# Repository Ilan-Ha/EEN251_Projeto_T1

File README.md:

# Bebedouro Inteligente para Pets

## Integrantes do Grupo:
- Diego Mourão Oliveira
- Ilan Hameiry
- Luca Lopes Martinho

## Descrição do Projeto

O projeto consiste no desenvolvimento de um dispositivo IoT voltado para o fornecimento de água corrente para animais de estimação (pets), com foco em uso residencial.

O objetivo principal é oferecer uma forma mais atrente e confortável de hidratação para o animal, simulando o fluxo de água corrente, além de monitorar a frequência com que o pet utiliza o bebedouro.

O sistema será ativado automaticamente apenas quando houver presença do animal próxima ao dispositivo, evitando desperdício de energia e água.

## Funcionamento do Sistema

O bebedouro funcionará em ciclo contínuo de circulação de água entre a bomba e o reservatório, simulando água corrente.

Por meio de um sensor de presença por distância (ultrassônico), o sistema será ativado automaticamente quando o animal se aproximar.

Após a detecção, o dispositivo permanecerá ligado por alguns segundos mesmo após a ausência de presença, garantindo tempo suficiente para o pet se hidratar.

Além disso, o sistema contará com:

- Iluminação interna por LEDs, acionada automaticamente quando a luminosidade do ambiente estiver baixa;
- Display informativo com dados importantes de uso;
- Monitoramento do nível de água no reservatório;
- Alertas de nível baixo de água;
- Botão de ativação manual;
- Botão de reset do sistema;
- Envio de notificações e informações para um software externo via Bluetooth.

## Objetivos do Projeto

- Melhorar a experiência de hidrtação dos pets;
- Automatizar o fornecimento de água;
- Reduzir desperdícios de energia e água;
- Permitir o monitoramento do uso do bebedouro;
- Fornecer alertas e informações em tempo real ao usuário.

## Requisitos do Sistema

### Requisitos Obrigatórios

| ID | Requisito | Tipo |
|---|---|---|
| RO-01 | Água circulando entre bomba e funil | Obrigatório |
| RO-02 | Detector de presença por distância (sensor ultrassônico) | Obrigatório |
| RO-03 | Iluminação em LED quando necessário | Obrigatório |
| RO-04 | Botão para ativação manual | Obrigatório |
| RO-05 | Botão de reset | Obrigatório |

### Requisitos Desejáveis

| ID | Requisito | Tipo |
|---|---|---|
| RD-01 | Display com informações úteis de uso: nível de água e número de ativações | Desejável |
| RD-02 | Mensagem via Bluetooth quando houver presença detectada ou nível baixo de água | Desejável |
| RD-03 | Sensor de nível de água | Desejável |

### Requisitos Opcionais

| ID | Requisito | Tipo |
|---|---|---|
| ROP-03 | Programação de ativação em intervalos de tempo definidos | Opcional |

## Diagrama de Blocos
```mermaid
flowchart TD
    MCU["Microcontrolador<br/>(Raspberry Pi Pico)"]

    OLED["Display<br/>OLED I2C<br/>128x32 Px"]
    RTC["Módulo Real Time Clock<br/>DS1307 (Opcional)"]
    LDR["Sensor de Luz<br/>LDR"]
    SOIL["Sensor de nível<br/>de água"]
    BT["Módulo Bluetooth<br/>HM10"]

    LEVEL1["Conversor de Nível Lógico<br/>(5V ↔ 3.3V)"]
    US["Sensor de Distância<br/>Ultrassom HC-SR04"]

    LEVEL2["Conversor de Nível Lógico<br/>(5V ↔ 3.3V)"]
    RELAY["Módulo Relé"]
    PUMP["Mini Bomba de Água<br/>DC-JT160"]

    MCU --> OLED 
    RTC --> MCU
    LDR --> MCU
    SOIL --> MCU
    MCU --> BT

    US --> LEVEL1
    LEVEL1 --> MCU

    MCU --> LEVEL2
    LEVEL2 --> RELAY
    RELAY --> PUMP

    %% Optional styling
    classDef sensor fill:#cfe8f3,stroke:#333,stroke-width:1px;
    classDef converter fill:#f4c542,stroke:#333,stroke-width:1px;
    classDef relay fill:#6abf4b,stroke:#333,stroke-width:1px;
    classDef controller fill:#cfe8f3,stroke:#333,stroke-width:2px;

    class MCU controller;
    class OLED,RTC,LDR,SOIL,BT,US,PUMP sensor;
    class LEVEL1,LEVEL2 converter;
    class RELAY relay;
    classDef default fill:#cfe8f3,color:#000,stroke:#000,stroke-width:2px;

    linkStyle default stroke:#000,stroke-width:2px;
```

## Softwares Utilizados

Durante o desenvolvimento do projeto foram utilizados os seguintes softwares:

- KiCad — utilizado para esquematização eletrônica e desenvolvimento do diagrama/layout da PCB;
- Thonny — utilizado para programação, testes e depuração do Raspberry Pi Pico;
- Autodesk Fusion 360, Solidworks — utilizados para modelagem 3D da estrutura do bebedouro;

## Tecnologias Envolvidas

O projeto utiliza conceitos de:

- Internet das Coisas (IoT)
- Sensores ultrassônicos
- Sensores de nível de água
- Iluminação automatizada com LEDs
- Comunicação via Bluetooth
- Sistemas embarcados
- Automação residencial

## Imagens do Modelo

| Vista Frontal | Vista Lateral |
| :---: | :---: |
|  |  |
| Vista Superior | Vista Isométrica |
|  |  |

## Apresentação do Projeto em Vídeo

Confira o funcionamento e a apresentação completa do Bebedouro Inteligente no vídeo abaixo:

[Clique aqui para assistir ao vídeo](https://youtu.be/lJpa5DYjjUw)

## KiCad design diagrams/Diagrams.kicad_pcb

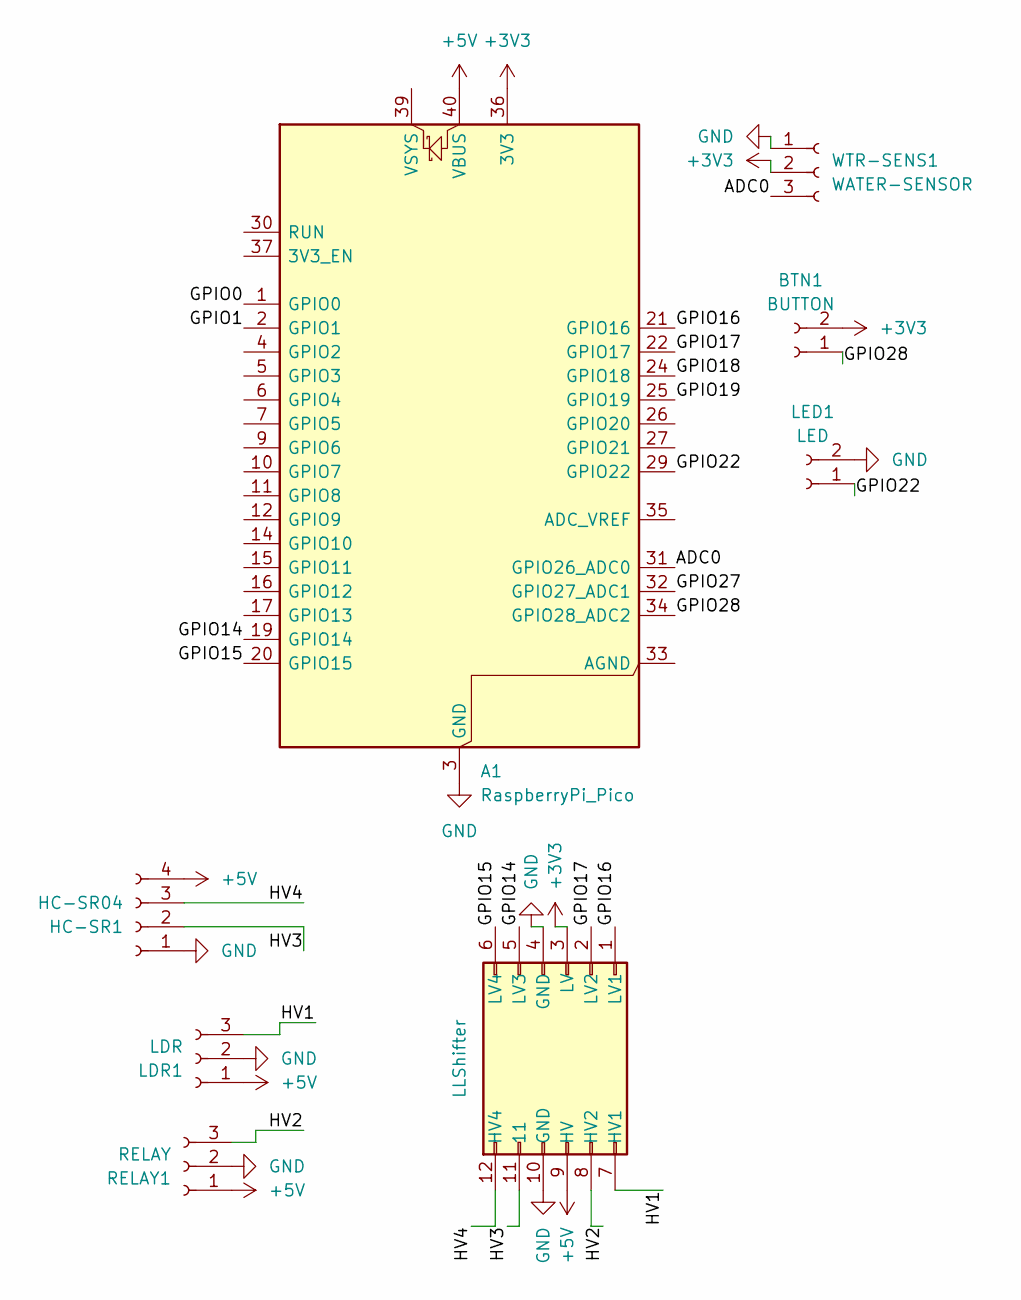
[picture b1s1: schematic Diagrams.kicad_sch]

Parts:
A1: RaspberryPi_Pico; RaspberryPi_Pico_Common_Unspecified
BTN1: BUTTON; SolderWire-0.25sqmm_1x02_P4.2mm_D0.65mm_OD1.7mm
HC-SR1: HC-SR04; SolderWire-0.25sqmm_1x04_P4.2mm_D0.65mm_OD1.7mm
LDR1: LDR; SolderWire-0.25sqmm_1x03_P4.2mm_D0.65mm_OD1.7mm
LED1: LED; SolderWire-0.25sqmm_1x02_P4.2mm_D0.65mm_OD1.7mm
LSA1: LLShifter; LLShifer-Footprint
RELAY1: RELAY; SolderWire-0.25sqmm_1x03_P4.2mm_D0.65mm_OD1.7mm
WTR-SENS1: WATER-SENSOR; SolderWire-0.25sqmm_1x03_P4.2mm_D0.65mm_OD1.7mm

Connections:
+3V3: A1.36 (3V3), BTN1.2 (IN), LSA1.3 (LV), WTR-SENS1.2 (VCC)
+5V: A1.40 (VBUS), HC-SR1.4 (VCC), LDR1.1 (VCC), LSA1.9 (HV), RELAY1.1 (VCC)
/ADC0: A1.31 (GPIO26_ADC0), WTR-SENS1.3 (SIGNAL)
/GPIO0: A1.1 (GPIO0)
/GPIO1: A1.2 (GPIO1)
/GPIO14: A1.19 (GPIO14), LSA1.5 (LV3)
/GPIO15: A1.20 (GPIO15), LSA1.6 (LV4)
/GPIO16: A1.21 (GPIO16), LSA1.1 (LV1)
/GPIO17: A1.22 (GPIO17), LSA1.2 (LV2)
/GPIO18: A1.24 (GPIO18)
/GPIO19: A1.25 (GPIO19)
/GPIO22: A1.29 (GPIO22), LED1.1 (GND)
/GPIO27: A1.32 (GPIO27_ADC1)
/GPIO28: A1.34 (GPIO28_ADC2), BTN1.1 (VCC)
/HV1: LDR1.3 (DO), LSA1.7 (HV1)
/HV2: LSA1.8 (HV2), RELAY1.3 (IN)
/HV3: HC-SR1.2 (ECHO), LSA1.11
/HV4: HC-SR1.3 (TRIG), LSA1.12 (HV4)
GND: A1.3 (GND), A1.8 (GND), A1.13 (GND), A1.18 (GND), A1.23 (GND), A1.28 (GND), A1.38 (GND), HC-SR1.1 (GND), LDR1.2 (GND), LED1.2 (VCC), LSA1.4 (GND), LSA1.10 (GND), RELAY1.2 (GND), WTR-SENS1.1 (GND)

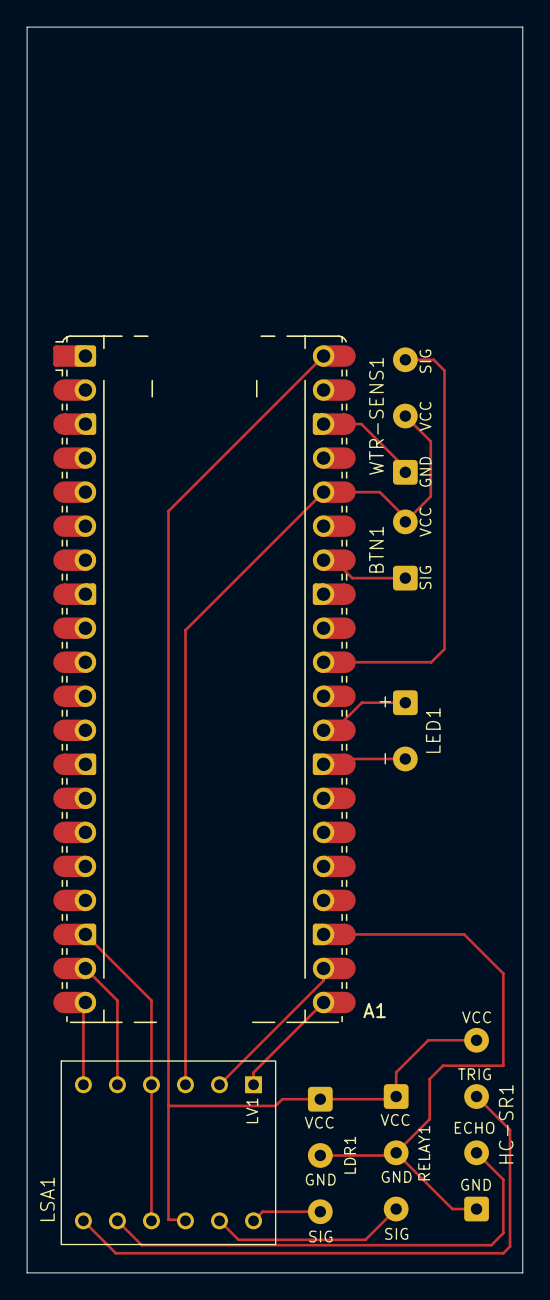
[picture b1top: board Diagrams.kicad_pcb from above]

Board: 2 copper layers, 37.0 x 93.0 mm, 8 parts (0 on the bottom side), 14 nets.

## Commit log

2026-04-19 feat: adiciona controle automático de relé com sensor ultrassônico e controle de led com sensor LDR
    - Sensor ultrassônico HC-SR04 para medição de distância em mm
    - Relé para posterior acionamento automático da bomba d’água
    - Sensor LDR para controle de iluminação com LED
    Funcionalidades adicionadas:
    - Envio de pulso e leitura de resposta do sensor ultrassônico
    - Cálculo da distância em milímetros sem uso de ponto flutuante
2026-04-19 Adiciona delay no controle do relé da bomba
    Foi adicionado um tempo de espera no acionamento e desligamento do relé da bomba utilizando sleep(), com as variáveis DELAY_RELAY_ON e DELAY_RELAY_OFF.
    Essa alteração evita que o relé desligue imediatamente quando o sensor ultrassônico deixa de detectar presença.
2026-04-19 Adiciona controle manual por botão e refatora lógica da bomba
    Foi implementado um botão para acionamento manual da bomba, permitindo ligar o relé independentemente da leitura do sensor ultrassônico.
    A antiga função control_pump_by_distance_mm() foi substituída por control_pump(), unificando a lógica de controle em uma única função. Agora, o botão manual possui prioridade sobre o modo automático,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
    Também foi adicionada a configuração Pin.PULL_DOWN no botão para evitar leituras instáveis no pino de entrada.
2026-04-22 feat: adiciona interrupcao ao ldr
2026-04-22 feat: adiciona deteccao de nivel de agua
2026-04-29 feat: adiciona pasta media com vídeos de testes do protótipo
    - adiciona vídeo demonstrando a detecção de movimento pelo sensor ultrassônico
    - adiciona vídeo demonstrando a detecção de baixa iluminação para acionamento dos LEDs
    - organiza arquivos de mídia para documentação e apresentação do projeto
2026-05-23 Adiciona diagramas do projeto feitos em KiCad
2026-05-23 feat(lib): adiciona biblioteca de footprints do KiCad
2026-05-24 update: mudança nos pinos led e button
2026-05-24 update: diagramas
    - alterações pequenas no diagrama esquemático
    - diagrama pcb inicial implementado
2026-05-27 update: novo esquemático
    - Esquemático refeito
    - Nova biblioteca adicionada
2026-05-27 udpate: mais algumas mudanças
2026-05-27 update: atribuição de footprints básicas na schematic
2026-05-27 update: altera botao e led onboard
    - Muda o comportamento do botão, anteriormente de segurar, para alternar.
    - Adição de led de debug ao pressionar o botão.
2026-05-28 deleta diagrams/een251.pretty directory
    - Não será utilizada mais.
2026-05-28 feat(pcb): finalizar layout da PCB pronto para impressão
    - concluir roteamento da placa
    - ajustar posicionamento dos módulos
    - corrigir outline da PCB em Edge.Cuts
    - prontificar PCB para fabricação/impressão
2026-05-28 refactor: atualizar mapeamento de GPIOs para corresponder ao da PCB
    - alterar pinos utilizados pelos módulos ldr, led, button, trigger, echo e relay no arquivo .py conforme organização física da placa
    - manter compatibilidade com o layout final para impressão
2026-05-28 docs(media): adicionar desenhos técnicos da carcaça do bebedouro
2026-05-28 Atualiza README com membros do grupo de detalhes dos softwares usados
2026-06-03 docs: adiciona bebedouro.stl
2026-06-03 docs: adiciona modelo do bebedouro
2026-06-03 feat: adiciona modelo do bebedouro
2026-06-03 Update(README): adiciona diagrama de blocos
2026-06-03 docs: adiciona gitkeep
2026-06-03 feat: adiciona fotos do bebedouro
2026-06-03 Update README.md: adiciona imagens
2026-06-03 refactor: modifica foto de vista superior
2026-06-04 Update README with project details and video link
    Added project presentation video link and updated project details.
